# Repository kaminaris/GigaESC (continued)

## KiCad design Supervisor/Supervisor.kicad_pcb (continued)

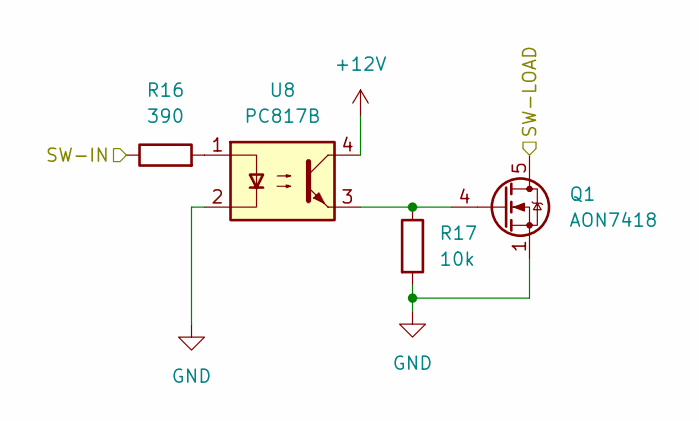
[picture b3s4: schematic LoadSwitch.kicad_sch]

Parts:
Q1: AON7418; VSON-8_3.3x3.3mm_P0.65mm_NexFET; MPN C74384
R16: 390; R_0603_1608Metric; MPN C23151
R17: 10k; R_0603_1608Metric; MPN C25804
U8: PC817B; SMDIP-4_W7.62mm; MPN C3025163

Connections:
+12V: U8.4; also elsewhere on the board
GND: Q1.1 (S), Q1.2 (S), Q1.3 (S), R17.2, U8.2; also elsewhere on the board
unnamed: Q1.4 (G), R17.1, U8.3
unnamed: R16.2, U8.1
SW1: R16.1; also elsewhere on the board
SW-LOAD-1: Q1.5 (D); also elsewhere on the board

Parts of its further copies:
Q2, Q3, Q4: AON7418; VSON-8_3.3x3.3mm_P0.65mm_NexFET; MPN C74384
R18, R20, R22: 390; R_0603_1608Metric; MPN C23151
R19, R21, R23: 10k; R_0603_1608Metric; MPN C25804
U9, U10, U11: PC817B; SMDIP-4_W7.62mm; MPN C3025163

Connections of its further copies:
+12V: U9.4, U10.4, U11.4; also elsewhere on the board
GND: Q2.1 (S), Q2.2 (S), Q2.3 (S), Q3.1 (S), Q3.2 (S), Q3.3 (S), Q4.1 (S), Q4.2 (S), Q4.3 (S), R19.2, R21.2, R23.2, U9.2, U10.2, U11.2; also elsewhere on the board
unnamed: Q2.4 (G), R19.1, U9.3
unnamed: Q3.4 (G), R21.1, U10.3
unnamed: Q4.4 (G), R23.1, U11.3
unnamed: R18.2, U9.1
unnamed: R20.2, U10.1
unnamed: R22.2, U11.1
SW2: R18.1; also elsewhere on the board
SW3: R20.1; also elsewhere on the board
SW4: R22.1; also elsewhere on the board
SW-LOAD-2: Q2.5 (D); also elsewhere on the board
SW-LOAD-3: Q3.5 (D); also elsewhere on the board
SW-LOAD-4: Q4.5 (D); also elsewhere on the board

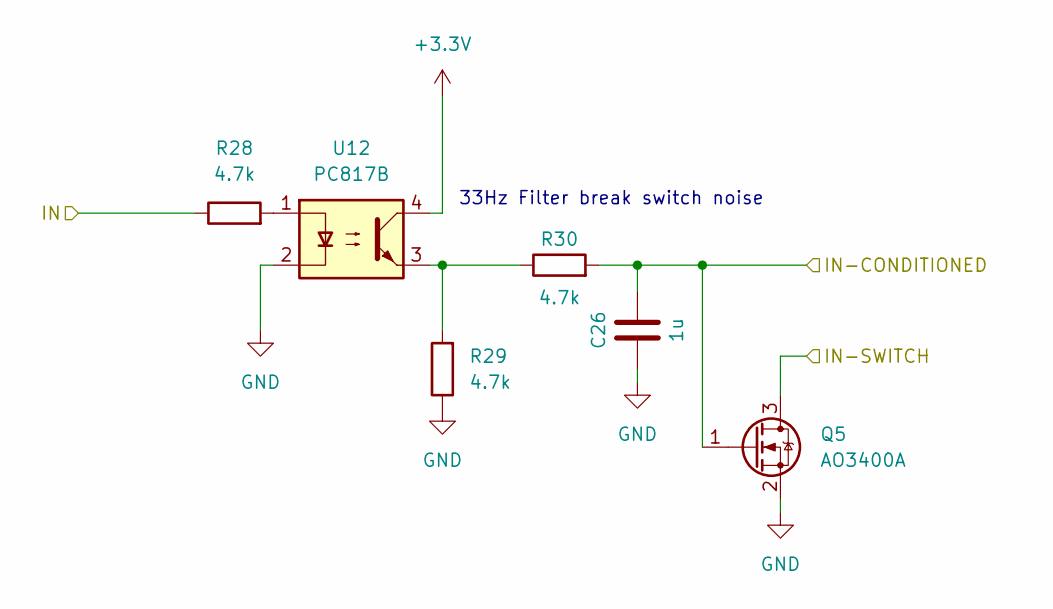
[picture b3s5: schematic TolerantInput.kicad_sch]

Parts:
C26: 1u; C_0603_1608Metric; MPN C15849
Q5: AO3400A; SOT-23; MPN C20917
R28, R29, R30: 4.7k; R_0603_1608Metric; MPN C23162
U12: PC817B; SMDIP-4_W7.62mm; MPN C3025163

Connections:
+3.3V: U12.4; also elsewhere on the board
D-IN-3: R28.1; also elsewhere on the board
DIGITAL-4-CLAMP: Q5.3 (D); also elsewhere on the board
GND: C26.2, Q5.2 (S), R29.1, U12.2; also elsewhere on the board
unnamed: R28.2, U12.1
unnamed: R29.2, R30.1, U12.3

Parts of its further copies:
C24: 1u; C_0603_1608Metric; MPN C15849
Q6: AO3400A; SOT-23; MPN C20917
R26, R27, R31: 4.7k; R_0603_1608Metric; MPN C23162
U13: PC817B; SMDIP-4_W7.62mm; MPN C3025163

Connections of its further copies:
+3.3V: U13.4; also elsewhere on the board
D-IN-4: R26.1; also elsewhere on the board
DIGITAL-3-CLAMP: Q6.3 (D); also elsewhere on the board
GND: C24.2, Q6.2 (S), R27.1, U13.2; also elsewhere on the board
unnamed: R26.2, U13.1
unnamed: R27.2, R31.1, U13.3

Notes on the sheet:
33Hz Filter break switch noise

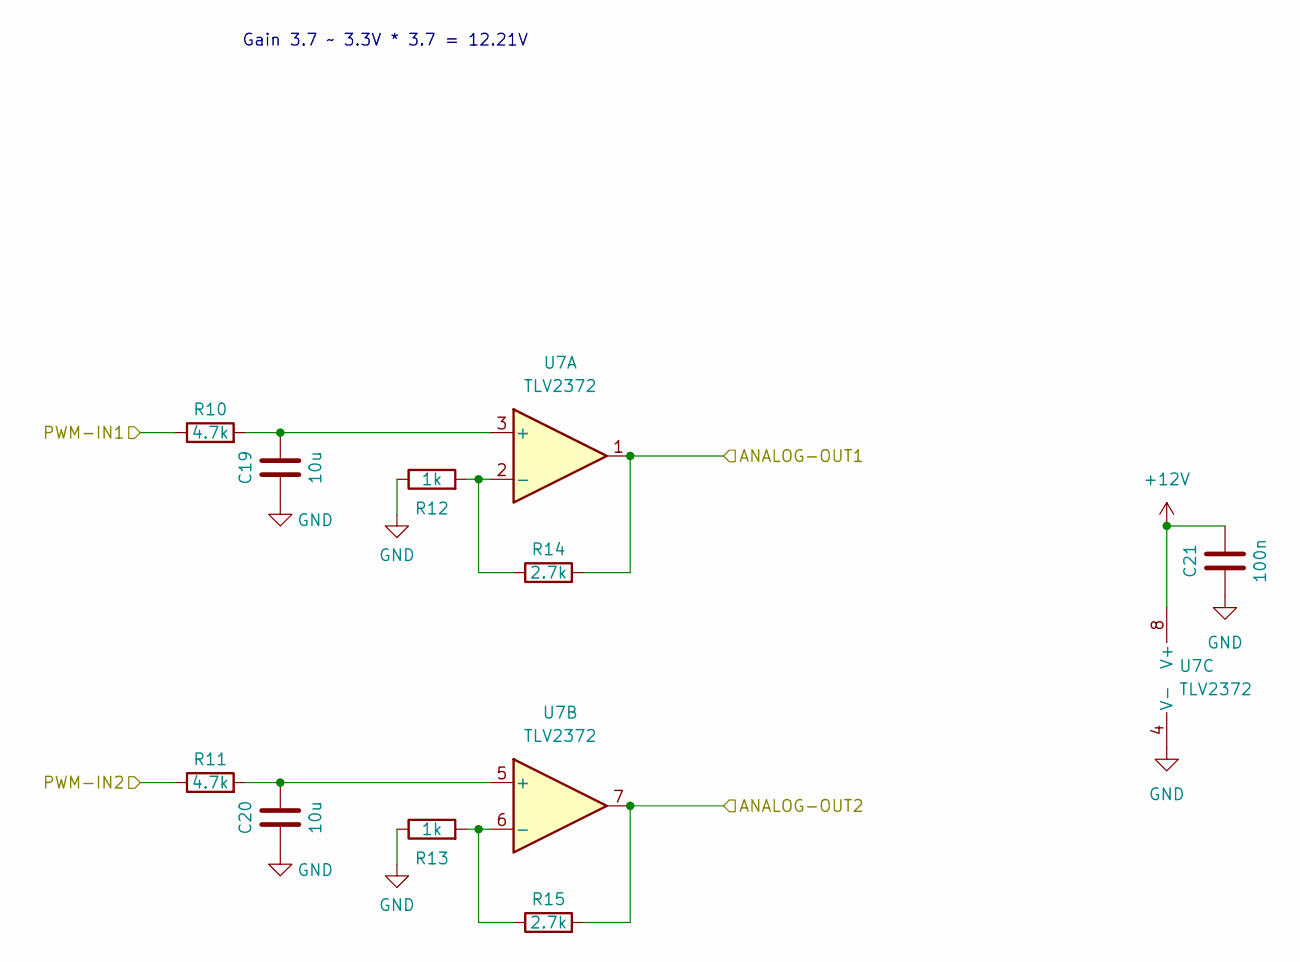
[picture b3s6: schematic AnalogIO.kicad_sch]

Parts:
C19, C20: 10u; C_0603_1608Metric; MPN C19702
C21: 100n; C_0603_1608Metric; MPN C14663
R10, R11: 4.7k; R_0603_1608Metric; MPN C23162
R12, R13: 1k; R_0603_1608Metric; MPN C21190
R14, R15: 2.7k; R_0603_1608Metric; MPN C13167
U7: TLV2372; SOIC-8_3.9x4.9mm_P1.27mm; MPN C27204

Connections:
+12V: C21.1, U7.8 (V+); also elsewhere on the board
AO1: R14.2, U7.1; also elsewhere on the board
AO2: R15.2, U7.7; also elsewhere on the board
GND: C19.2, C20.2, C21.2, R12.1, R13.1, U7.4 (V-); also elsewhere on the board
unnamed: C19.1, R10.2, U7.3 (+)
unnamed: R12.2, R14.1, U7.2 (-)
unnamed: C20.1, R11.2, U7.5 (+)
unnamed: R13.2, R15.1, U7.6 (-)
PWM1: R10.1; also elsewhere on the board
PWM2: R11.1; also elsewhere on the board

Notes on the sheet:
Gain 3.7 ~ 3.3V * 3.7 = 12.21V

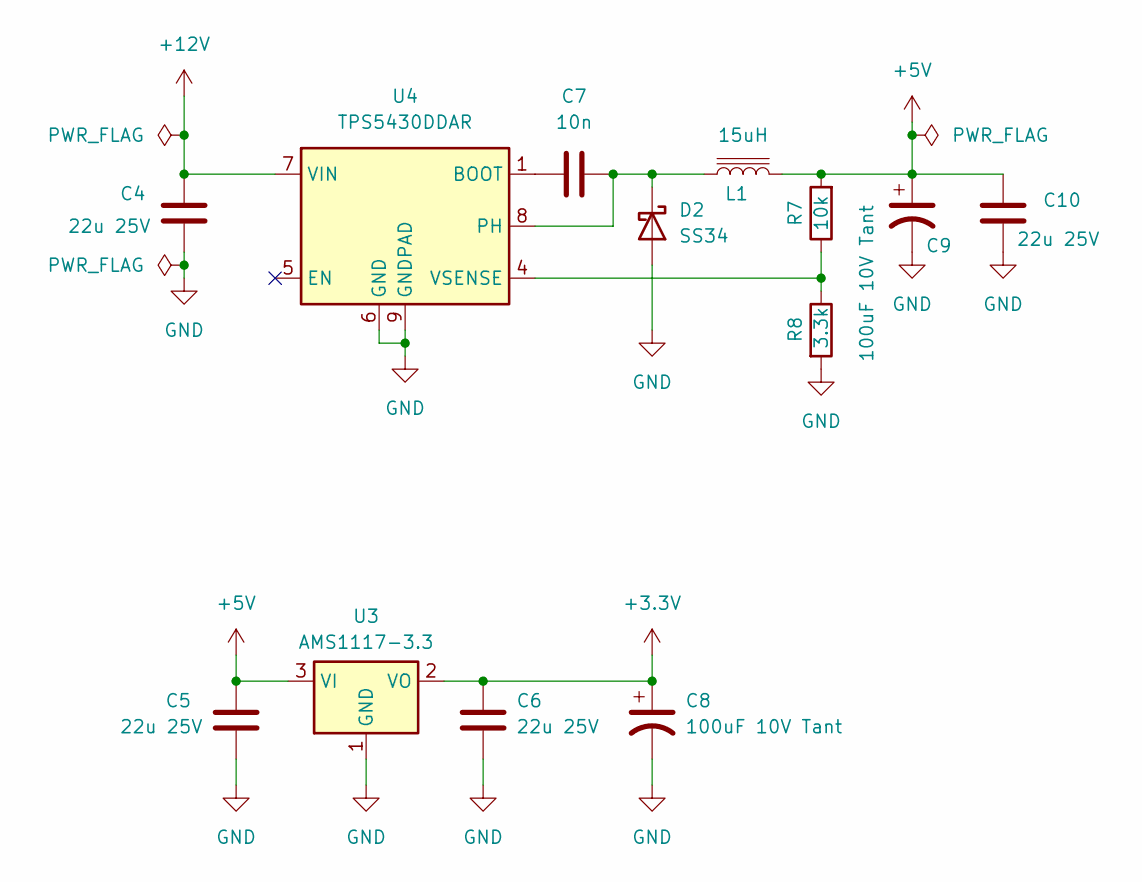
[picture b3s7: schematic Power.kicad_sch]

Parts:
C4, C5, C6, C10: 22u 25V; C_1206_3216Metric; MPN C12891
C7: 10n; C_0603_1608Metric; MPN C57112
C8, C9: 100uF 10V Tant; CP_EIA-6032-28_Kemet-C; MPN C171664; JLCRotOffset -180
D2: SS34; D_SMA; MPN C8678
L1: 15uH; L_Bourns_SRP7028A_7.3x6.6mm; MPN C177243
R7: 10k; R_0603_1608Metric; MPN C25804
R8: 3.3k; R_0603_1608Metric; MPN C22978
U3: AMS1117-3.3; SOT-223-3_TabPin2; MPN C6186; JLCRotOffset -180
U4: TPS5430DDAR; TI_SO-PowerPAD-8_ThermalVias; MPN C9864

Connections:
+3.3V: C6.1, C8.1, U3.2 (VO); also elsewhere on the board
+5V: C5.1, C9.1, C10.1, L1.2, R7.2, U3.3 (VI); also elsewhere on the board
+12V: C4.1, U4.7 (VIN); also elsewhere on the board
GND: C4.2, C5.2, C6.2, C8.2, C9.2, C10.2, D2.2 (A), R8.2, U3.1 (GND), U4.6 (GND), U4.9 (GNDPAD); also elsewhere on the board
unnamed: C7.1, D2.1 (K), L1.1, U4.8 (PH)
unnamed: C7.2, U4.1 (BOOT)
unnamed: R7.1, R8.1, U4.4 (VSENSE)

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
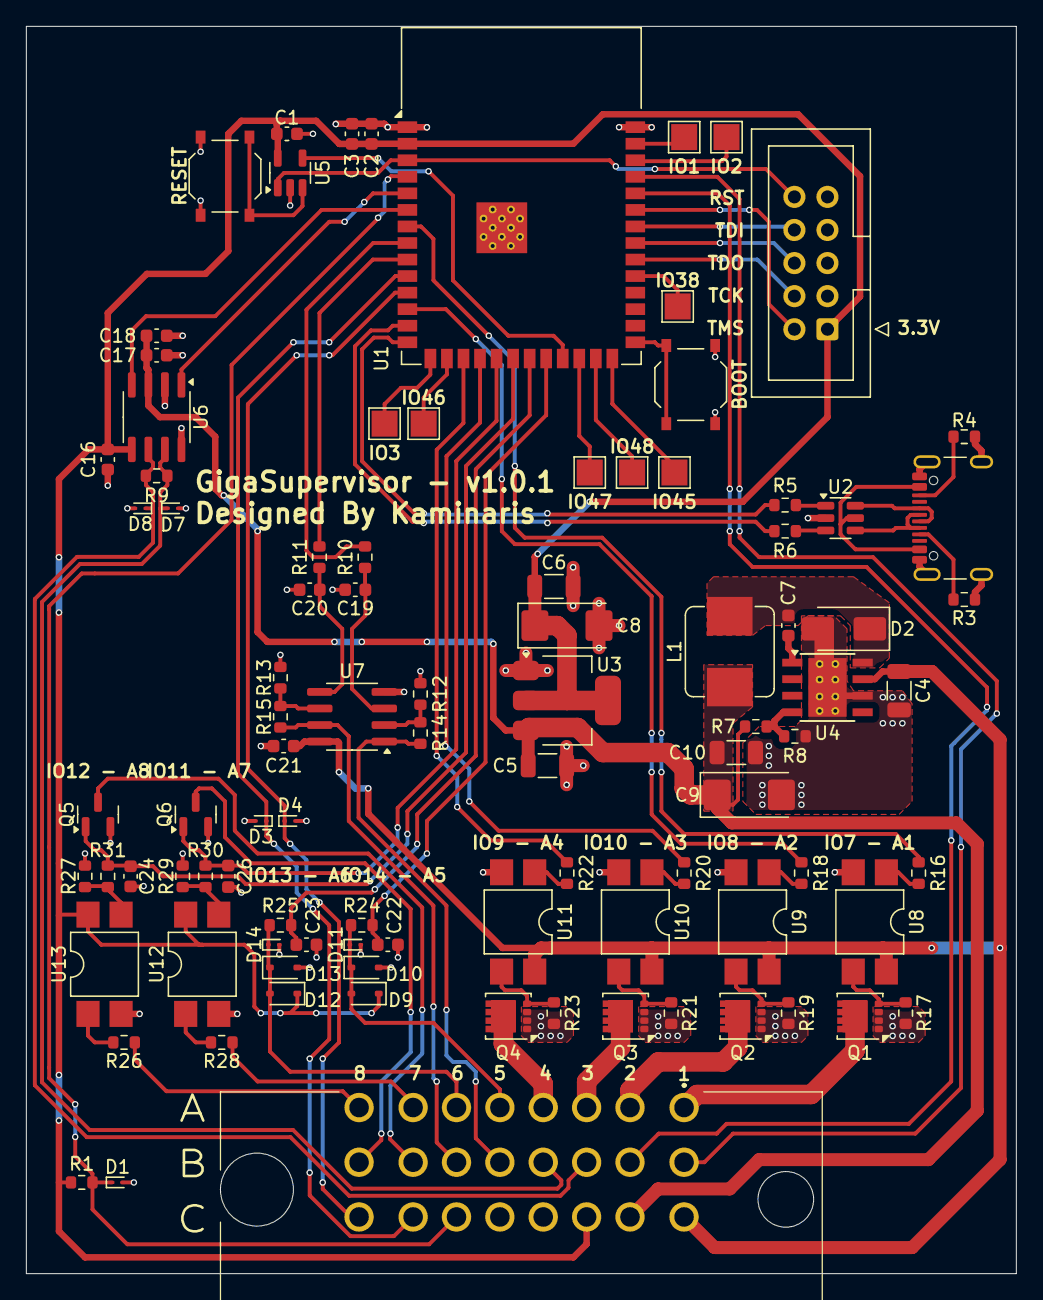
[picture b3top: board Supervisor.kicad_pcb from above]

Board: 2 copper layers, 76.0 x 95.8 mm, 97 parts (0 on the bottom side), 79 nets.

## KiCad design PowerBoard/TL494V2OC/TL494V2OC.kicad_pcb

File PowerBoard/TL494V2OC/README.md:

# Power Supply TL494 V2

Version without power switch

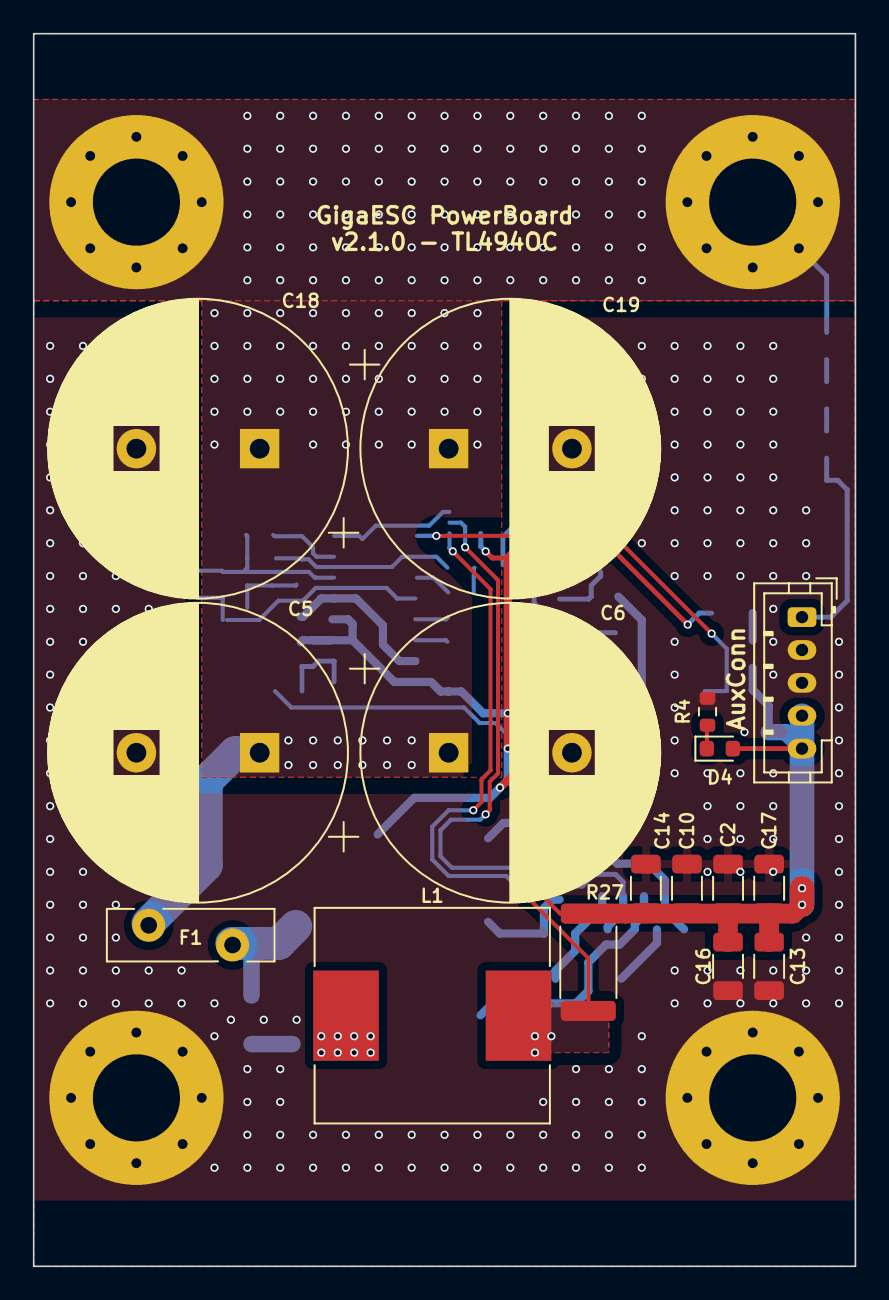
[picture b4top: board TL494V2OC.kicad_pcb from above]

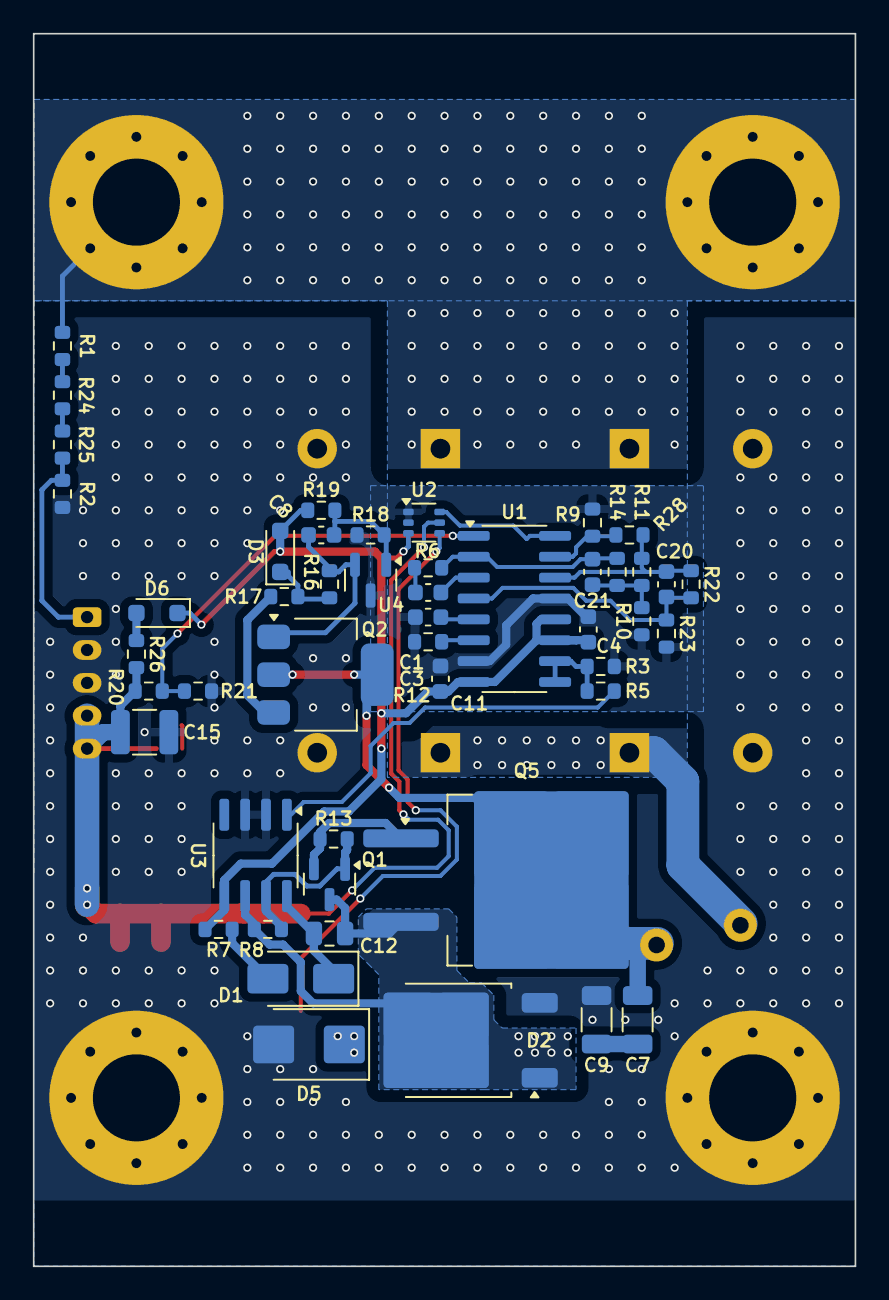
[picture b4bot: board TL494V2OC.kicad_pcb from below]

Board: 2 copper layers, 50.0 x 75.0 mm, 68 parts (48 on the bottom side), 34 nets.

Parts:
C1, C4, C21: 100n; C_0603_1608Metric
C2, C10, C13, C14, C16, C17: 22u; C_1206_3216Metric
C3, C8: 1n; C_0603_1608Metric
C5, C6, C18, C19: 330u 200V; CP_Radial_D18.0mm_P7.50mm
C7, C9: 2.2u 100V; C_1206_3216Metric
C11: 1u; C_0603_1608Metric
C12: 100n 200V; C_0805_2012Metric
C15: 47u 16V; C_1210_3225Metric
C20: 10u; C_0603_1608Metric
D1: SS520F; D_SMA
D2: CI04S65E3; TO-252-2
D3: BZT52C5V1S; D_SOD-323_HandSoldering
D4: RUN; D_0603_1608Metric
D5: BZG03C16-M3-08; D_SMB
D6: 1N5819WS; D_SOD-323_HandSoldering
F1: RLVR240-100; Fuse_Bourns_MF-RHT400
H1, H2, H3, H4: MountingHole_Pad; MountingHole_5.3mm_M5_Pad_Via
J1: AuxConn; JST_PH_B5B-PH-K_1x05_P2.00mm_Vertical
L1: 100uH; L_Chilisin_BMRG00131360
Q1: MMBTA92; SOT-23
Q2: CPC3980; SOT-223-3_TabPin2
Q5: IRFS4227TRLPBF; TO-263-2
R1, R24, R25: 348k; R_0603_1608Metric
R2: 18.7k; R_0603_1608Metric
R3, R16, R22: 10k; R_0603_1608Metric
R4: 82k; R_0603_1608Metric
R5: 100; R_0603_1608Metric
R6: 2k; R_0603_1608Metric
R7, R13, R26: 22; R_0603_1608Metric
R8: 1k; R_0603_1608Metric
R9, R10, R11, R12: 5.1k; R_0603_1608Metric
R14: 200k; R_0603_1608Metric
R17: 47; R_0603_1608Metric
R18: 9.1k; R_0603_1608Metric
R19: 30k; R_0603_1608Metric
R20: 100k; R_0603_1608Metric
R21: 27k; R_0603_1608Metric
R23: 4.7k; R_0603_1608Metric
R27: 10m; R_2512_6332Metric
R28: 20k; R_0603_1608Metric
U1: TL494; SOIC-16_3.9x9.9mm_P1.27mm
U2: INA213; SOT-363_SC-70-6
U3: IR2181; SOIC-8_3.9x4.9mm_P1.27mm
U4: TL431; SOT-23

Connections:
+12V: C2.1, C10.1, C13.1, C14.1, C15.1, C16.1, C17.1, D4.2 (A), J1.4, J1.5, R20.1, R26.1, R27.2, U2.5 (-)
+BATT: C5.1, C6.1, C18.1, C19.1, F1.1, H2.1, H4.1, R1.1
+VSW: C7.1, F1.2, Q2.2 (D), Q5.2 (D)
-BATT: C2.2, C3.2, C4.2, C5.2, C6.2, C9.2, C10.2, C11.2, C13.2, C14.2, C15.2, C16.2, C17.2, C18.2, C19.2, D2.3 (A), D5.2 (A), H1.1, H3.1, J1.2, J1.3, R2.2, R3.2, R4.1, R9.2, R10.2, R12.2, R18.2, R21.2, R23.2, U1.7 (GND), U1.13 (OUTCTRL), U2.1 (REF), U2.2 (GND), U3.2 (LIN), U3.3 (COM), U4.3 (A)
/SW-NODE: C12.2, D2.1 (K), D2.2 (K), L1.1, Q1.3 (C), Q5.3 (S), R8.1, U3.6 (VS)
CFB: U1.16 (2IN+), U2.6
CFB-: R9.1, R28.2, U1.15 (2IN-)
DRV-OUT: Q1.1 (B), R8.2, R13.1, U3.7 (HO)
IN_V: J1.1, R2.1, R25.2
unnamed: C1.1, R6.2
unnamed: C7.2, C9.1
unnamed: C21.2, R10.1, R11.2, R14.2
unnamed: D1.2 (A), R7.2
unnamed: C12.1, D1.1 (K), U3.8 (VB)
unnamed: D3.1 (K), R16.1, R17.2
unnamed: D4.1 (K), R4.2
unnamed: D5.1 (K), L1.2, R27.1, U2.4 (+)
unnamed: D6.2 (A), R26.2
unnamed: Q1.2 (E), Q5.1 (G), R13.2
unnamed: C8.1, Q2.1 (G), R16.2, U4.2 (K)
unnamed: Q2.3 (S), R17.1
unnamed: R1.2, R24.1
unnamed: R24.2, R25.1
unnamed: C21.1, R6.1, R14.1, U1.2 (1IN-)
unnamed: C3.1, U1.5 (CT)
unnamed: C20.2, R22.2, R23.1, U1.4 (DTC)
unnamed: R3.1, R5.2, U1.9 (E1), U1.10 (E2)
unnamed: C1.2, U1.3 (FB)
unnamed: C20.1, R11.1, R22.1, R28.1, U1.14 (REF)
unnamed: R12.1, U1.6 (RT)
unnamed: R5.1, U3.1 (HIN)
unnamed: C8.2, R18.1, R19.1, U4.1 (R)
STARTUP: C4.1, C11.1, D3.2 (A), D6.1 (K), R7.1, R19.2, U1.8 (C1), U1.11 (C2), U1.12 (VCC), U2.3 (V+), U3.5 (VCC)
VFB: R20.2, R21.1, U1.1 (1IN+)

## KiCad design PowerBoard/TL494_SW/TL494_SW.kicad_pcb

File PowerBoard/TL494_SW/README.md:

# Power Supply TL494

Version with power switch

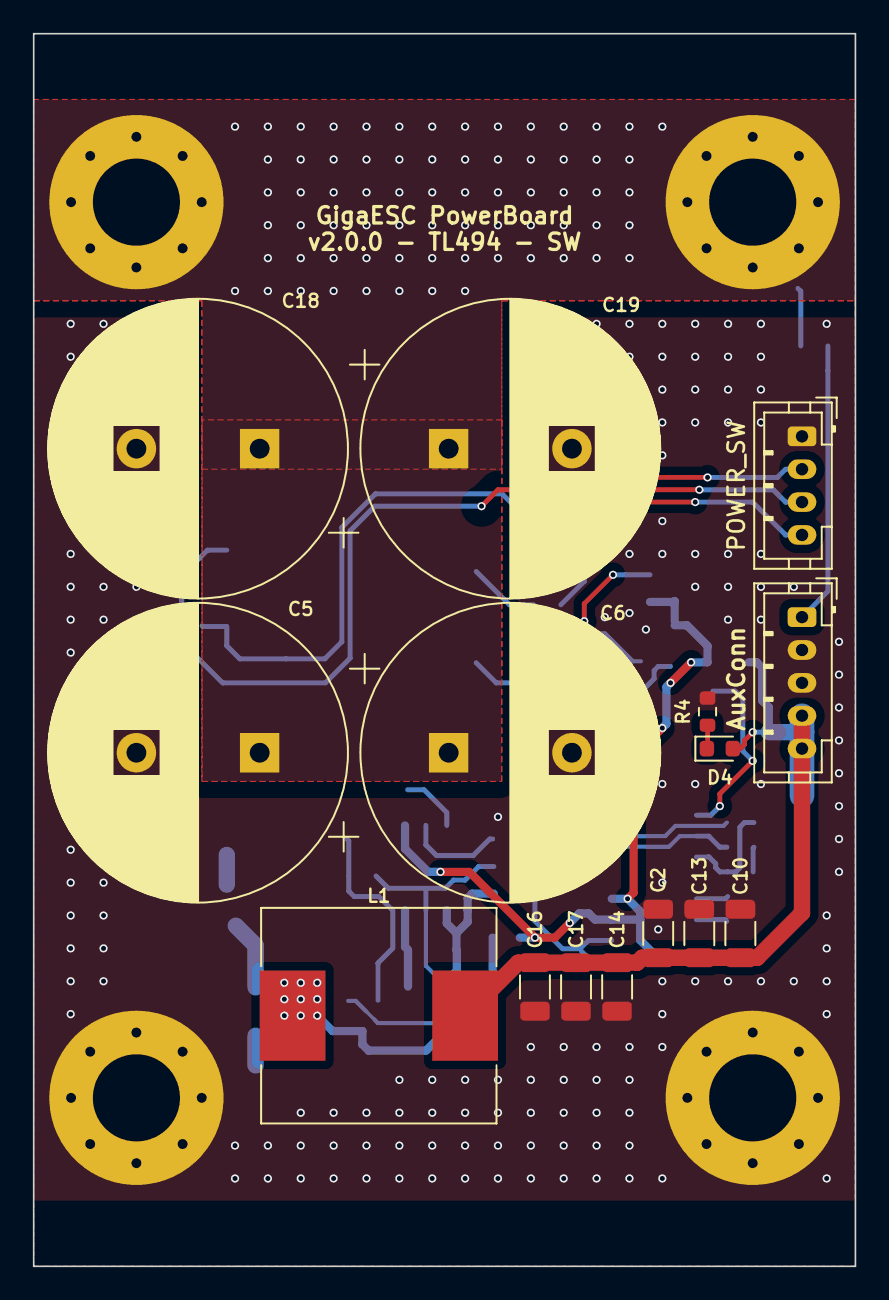
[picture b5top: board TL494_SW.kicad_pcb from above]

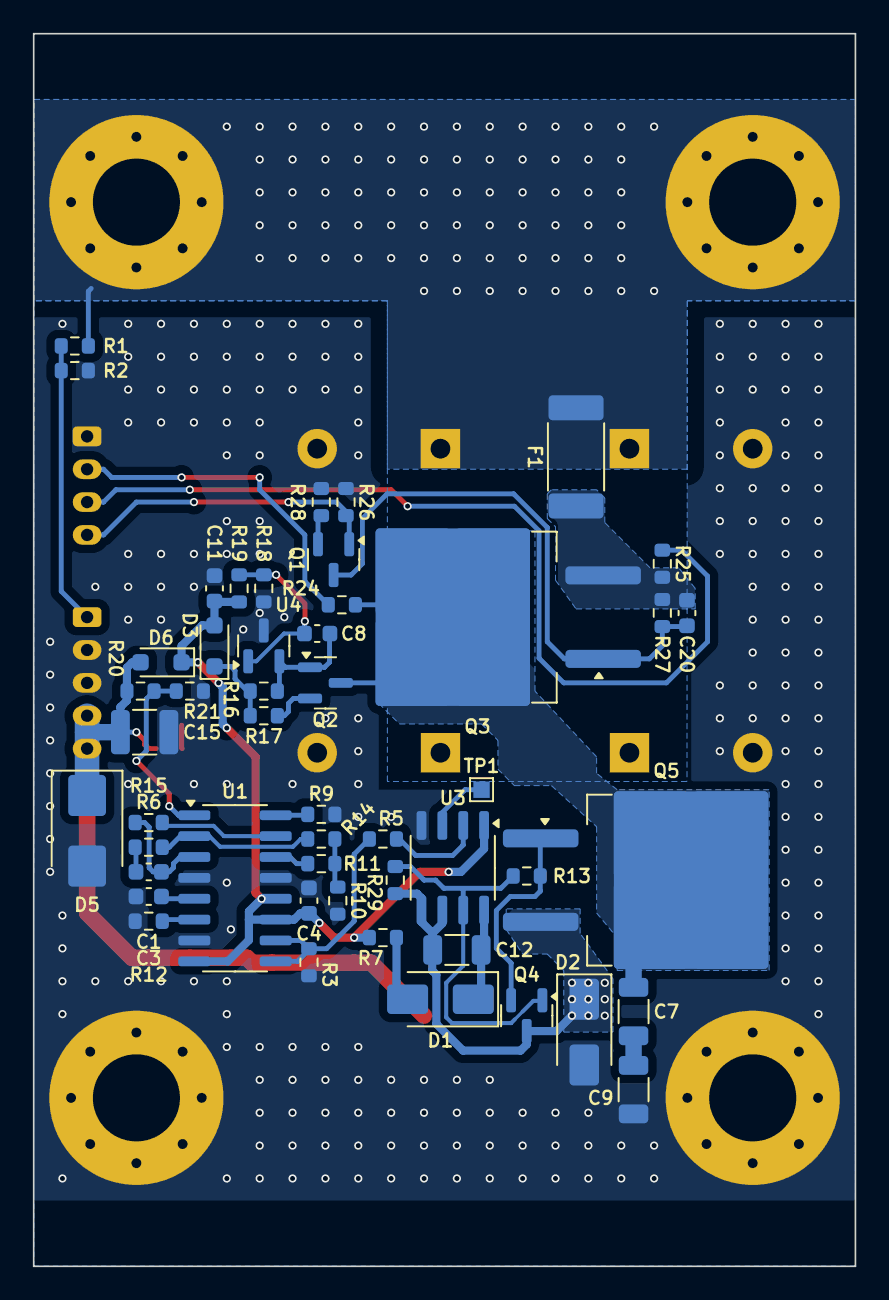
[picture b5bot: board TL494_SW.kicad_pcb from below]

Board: 2 copper layers, 50.0 x 75.0 mm, 69 parts (50 on the bottom side), 36 nets.

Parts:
C1, C4, C20: 100n; C_0603_1608Metric
C2, C10, C13, C14, C16, C17: 22u; C_1206_3216Metric
C3, C8: 1n; C_0603_1608Metric
C5, C6, C18, C19: 330u 200V; CP_Radial_D18.0mm_P7.50mm
C7, C9: 2.2u 100V; C_1206_3216Metric
C11: 1u; C_0603_1608Metric
C12: 220n; C_1206_3216Metric
C15: 47u 16V; C_1210_3225Metric
D1, D2: SS520F; D_SMA
D3: BZT52C5V1S; D_SOD-323_HandSoldering
D4: RUN; D_0603_1608Metric
D5: 3SMB5928B; D_SMB
D6: 1N5819WS; D_SOD-323_HandSoldering
F1: Fuse; Fuse_2512_6332Metric_Pad1.52x3.35mm_HandSolder
H1, H2, H3, H4: MountingHole_Pad; MountingHole_5.3mm_M5_Pad_Via
J1: AuxConn; JST_PH_B5B-PH-K_1x05_P2.00mm_Vertical
J2: POWER_SW; JST_PH_B4B-PH-K_1x04_P2.00mm_Vertical
L1: 100uH; L_Chilisin_BMRG00131360
Q1: MMBTA42; SOT-23
Q2: BSS126; SOT-23
Q3: IRF9640SPBF; TO-263-2
Q4: S9012 2T1; SOT-23
Q5: IRFS4227TRLPBF; TO-263-2
R1: 150k; R_0603_1608Metric
R2, R21: 2.7k; R_0603_1608Metric
R3, R15, R16, R18, R20: 10k; R_0603_1608Metric
R4: 82k; R_0603_1608Metric
R5, R9, R17: 100; R_0603_1608Metric
R6: 2k; R_0603_1608Metric
R7, R13: 22; R_0603_1608Metric
R10, R11, R12: 5.1k; R_0603_1608Metric
R14, R25: 200k; R_0603_1608Metric
R19: 30k; R_0603_1608Metric
R24, R27: 100k; R_0603_1608Metric
R26: 20k; R_0603_1608Metric
R28: 27k; R_0603_1608Metric
R29: 1k; R_0603_1608Metric
TP1: TestPoint; TestPoint_Pad_1.0x1.0mm
U1: TL494; SOIC-16_3.9x9.9mm_P1.27mm
U3: IRS21271; SO-8_3.9x4.9mm_P1.27mm
U4: TL431; SOT-23

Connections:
+12V: C2.1, C10.1, C13.1, C14.1, C15.1, C16.1, C17.1, D4.2 (A), D5.1 (K), D6.2 (A), J1.4, J1.5, L1.2, R20.2
+BATT: C5.1, C6.1, C18.1, C19.1, F1.1, H2.1, H4.1, R1.1
+VSW: C7.1, Q2.3 (D), Q3.2 (D), Q5.2 (D), R24.2
-BATT: C2.2, C3.2, C4.2, C5.2, C6.2, C9.2, C10.2, C11.2, C13.2, C14.2, C15.2, C16.2, C17.2, C18.2, C19.2, D2.2 (A), D5.2 (A), H1.1, H3.1, J1.2, J1.3, J2.1, R2.2, R3.2, R4.1, R9.1, R10.2, R12.2, R18.1, R21.1, R26.2, R28.2, U1.4 (DTC), U1.7 (GND), U1.13 (OUTCTRL), U3.4 (COM), U4.3 (A)
BOOTSTRAP: C4.1, C11.1, D3.2 (A), D6.1 (K), R7.1, R19.2, U1.8 (C1), U1.11 (C2), U1.12 (VCC), U3.1 (VCC)
IN_V: J1.1, R1.2, R2.1
unnamed: C1.1, R6.2
unnamed: C7.2, C9.1
unnamed: D1.2 (A), R7.2
unnamed: C12.1, D1.1 (K), U3.8 (VB)
unnamed: C12.2, D2.1 (K), L1.1, Q4.3 (C), Q5.3 (S), R29.1, U3.5 (VS), U3.6 (CS)
unnamed: D3.1 (K), R16.1, R17.1
unnamed: D4.1 (K), R4.2
unnamed: J2.2, R24.1
unnamed: J2.3, R25.2
unnamed: J2.4, Q1.1 (B), R26.1
unnamed: C20.2, Q1.3 (C), Q3.1 (G), R27.2
unnamed: Q1.2 (E), R28.1
unnamed: C8.1, Q2.1 (G), R16.2, U4.2 (K)
unnamed: Q2.2 (S), R17.2
unnamed: C20.1, F1.2, Q3.3 (S), R25.1, R27.1
unnamed: Q4.1 (B), R13.1, R29.2, U3.7 (HO)
unnamed: Q4.2 (E), Q5.1 (G), R13.2
unnamed: R10.1, R11.2, R14.2
unnamed: R6.1, R14.1, U1.2 (1IN-)
unnamed: R9.2, U1.16 (2IN+)
unnamed: R15.2, U1.15 (2IN-)
unnamed: C3.1, U1.5 (CT)
unnamed: R3.1, R5.2, U1.9 (E1), U1.10 (E2)
unnamed: C1.2, R15.1, U1.3 (FB)
unnamed: R11.1, U1.14 (REF)
unnamed: R12.1, U1.6 (RT)
unnamed: TP1.1, U3.3 (FAULT)
unnamed: R5.1, U3.2 (IN)
unnamed: C8.2, R18.2, R19.1, U4.1 (R)
VFB: R20.1, R21.2, U1.1 (1IN+)

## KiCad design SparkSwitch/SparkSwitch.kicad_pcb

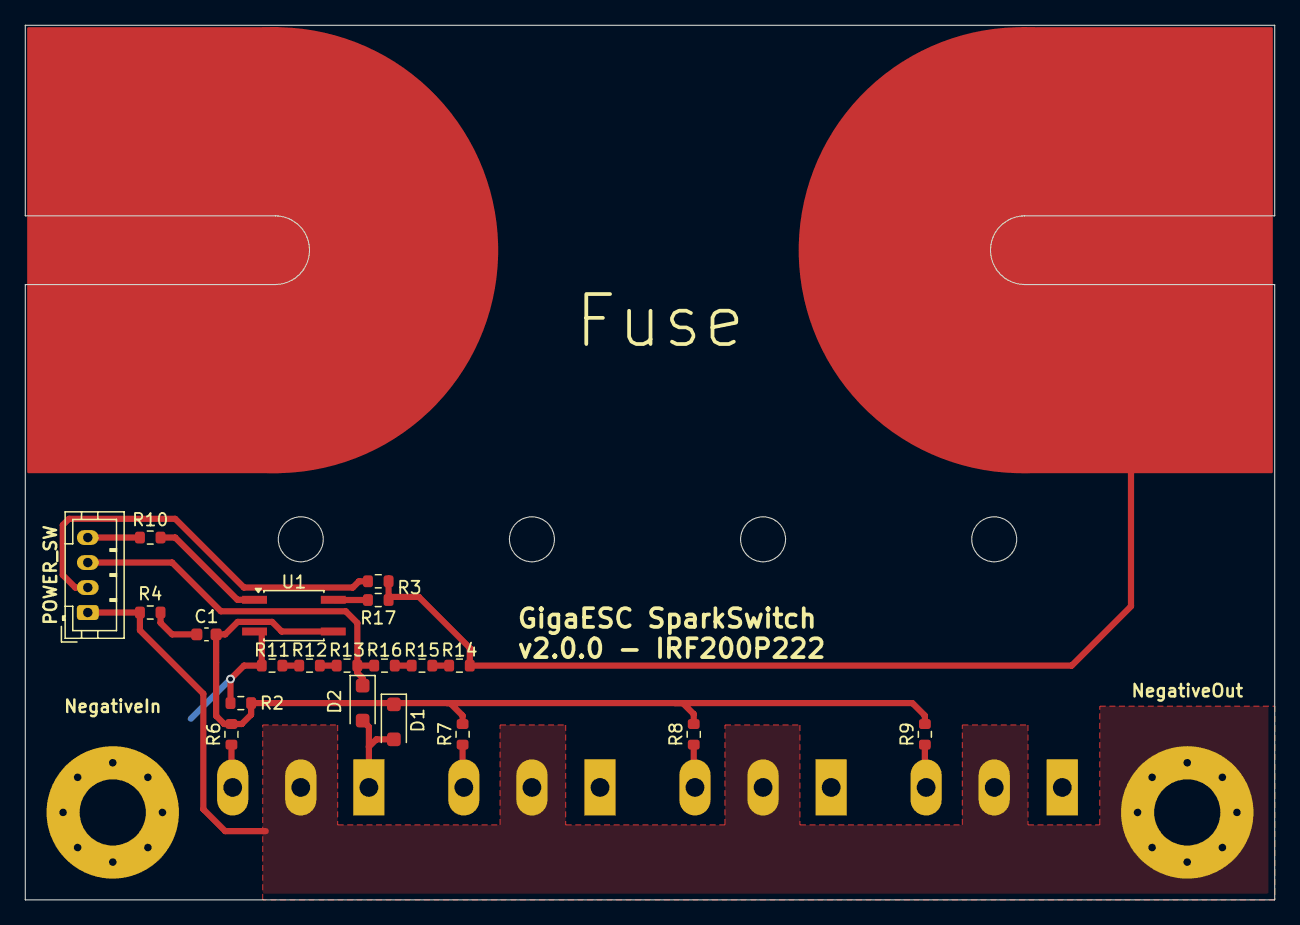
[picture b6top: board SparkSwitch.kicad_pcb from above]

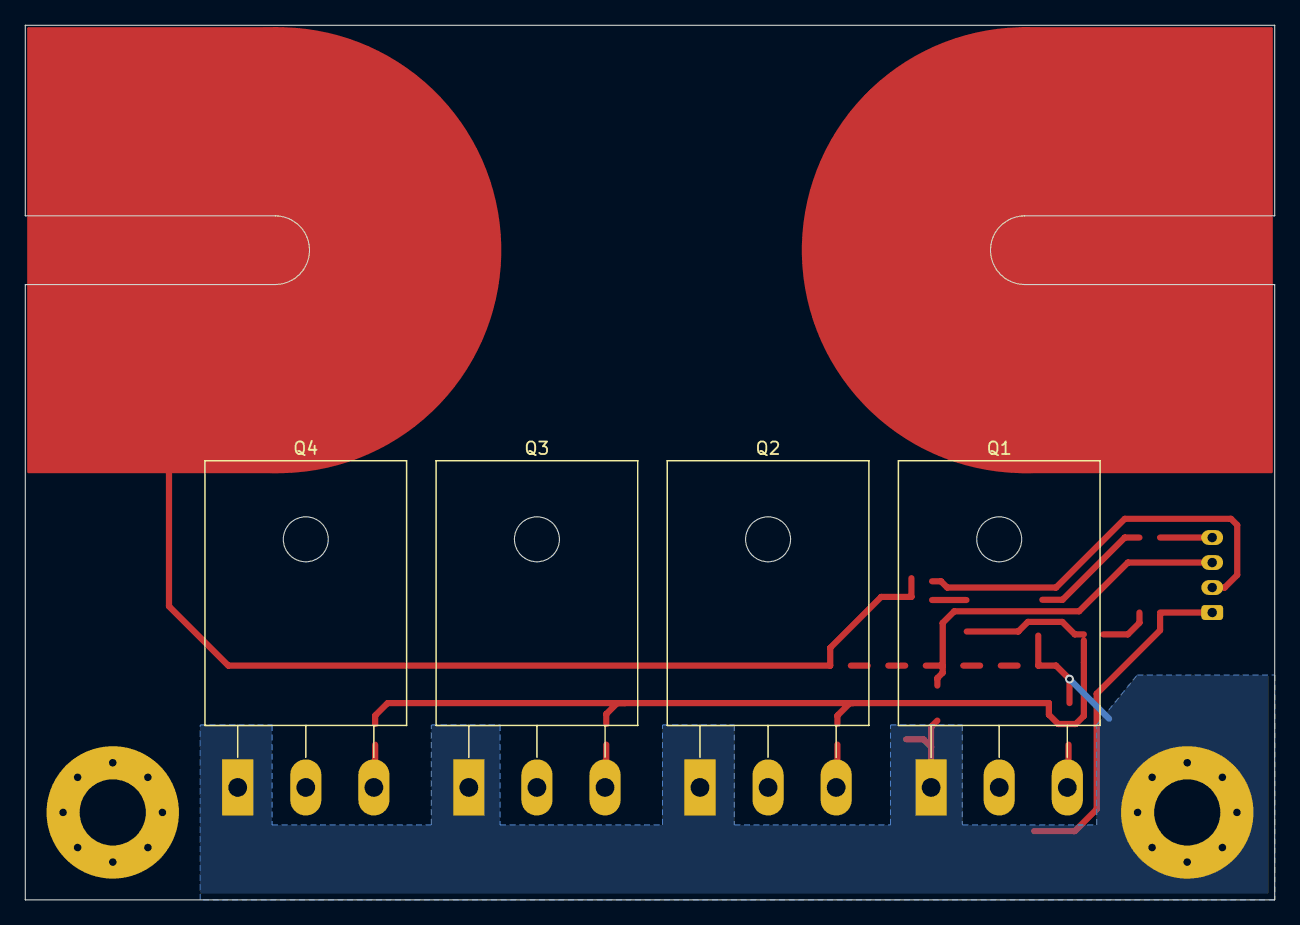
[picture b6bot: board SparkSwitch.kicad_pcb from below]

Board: 2 copper layers, 100.0 x 70.0 mm, 27 parts (4 on the bottom side), 18 nets.

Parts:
C1: 1u; C_0603_1608Metric
D1, D2: BZT52B12; D_SOD-123F
J3: POWER_SW; JST_PH_B4B-PH-K_1x04_P2.00mm_Vertical
J5: NegativeIn; MountingHole_5.3mm_M5_Pad_Via
J7: NegativeOut; MountingHole_5.3mm_M5_Pad_Via
Q1, Q2, Q3, Q4: IRF200P222; TO-247-3_Horizontal_TabDown
R2: 10k; R_0603_1608Metric
R3, R11, R12, R13, R14, R15, R16: 100k; R_0603_1608Metric
R4, R17: 1k; R_0603_1608Metric
R6, R7, R8, R9, R10: 22; R_0603_1608Metric
TP1: TestPoint; TestPoint_Pad_1.0x1.0mm
U1: LTV-352T; SO-4_4.4x3.6mm_P2.54mm

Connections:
+VSW: R3.2, R14.1, R17.1
-BATT: J3.1, J7.1, Q1.2 (D), Q2.2 (D), Q3.2 (D), Q4.2 (D), R4.2
GND: D1.2 (A), D2.2 (A), J5.1, Q1.1 (S), Q2.1 (S), Q3.1 (S), Q4.1 (S), R2.2, R11.2, U1.2
unnamed: C1.1, R4.1
unnamed: C1.2, D1.1 (K), R2.1, R6.2, R7.2, R8.2, R9.2, U1.3
unnamed: J3.2, R3.1
unnamed: Q1.3 (G), R6.1
unnamed: Q2.3 (G), R7.1
unnamed: Q3.3 (G), R8.1
unnamed: Q4.3 (G), R9.1
unnamed: R10.2, U1.1
unnamed: R11.1, R12.2
unnamed: R12.1, R13.2
unnamed: R14.2, R15.1
unnamed: R15.2, R16.1
unnamed: R17.2, U1.4
SW_NC: J3.4, R10.1
SW_NX: D2.1 (K), J3.3, R13.1, R16.2

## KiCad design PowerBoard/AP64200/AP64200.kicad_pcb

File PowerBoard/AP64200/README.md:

# Power Supply AP64200

## ⚠ Not working - Do not use ⚠

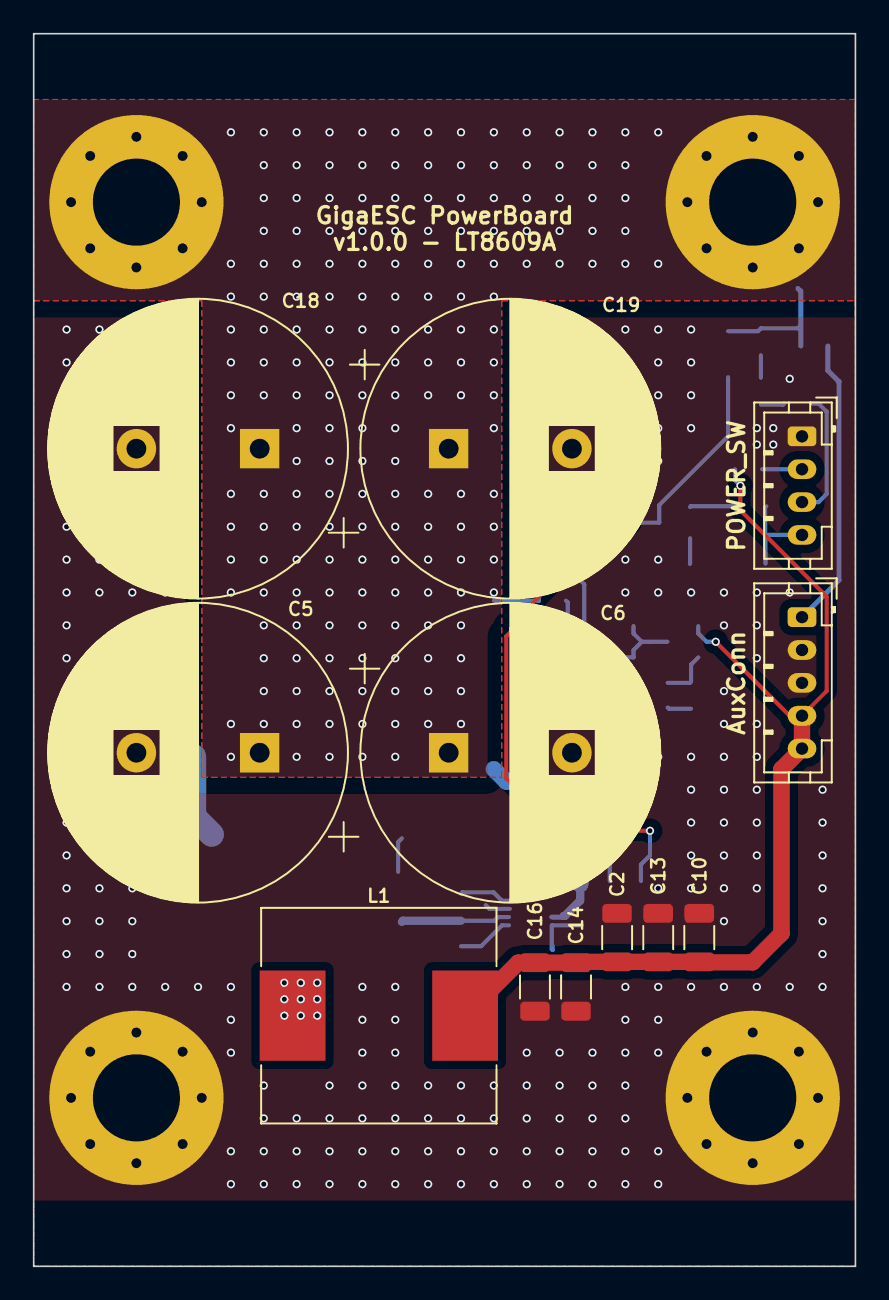
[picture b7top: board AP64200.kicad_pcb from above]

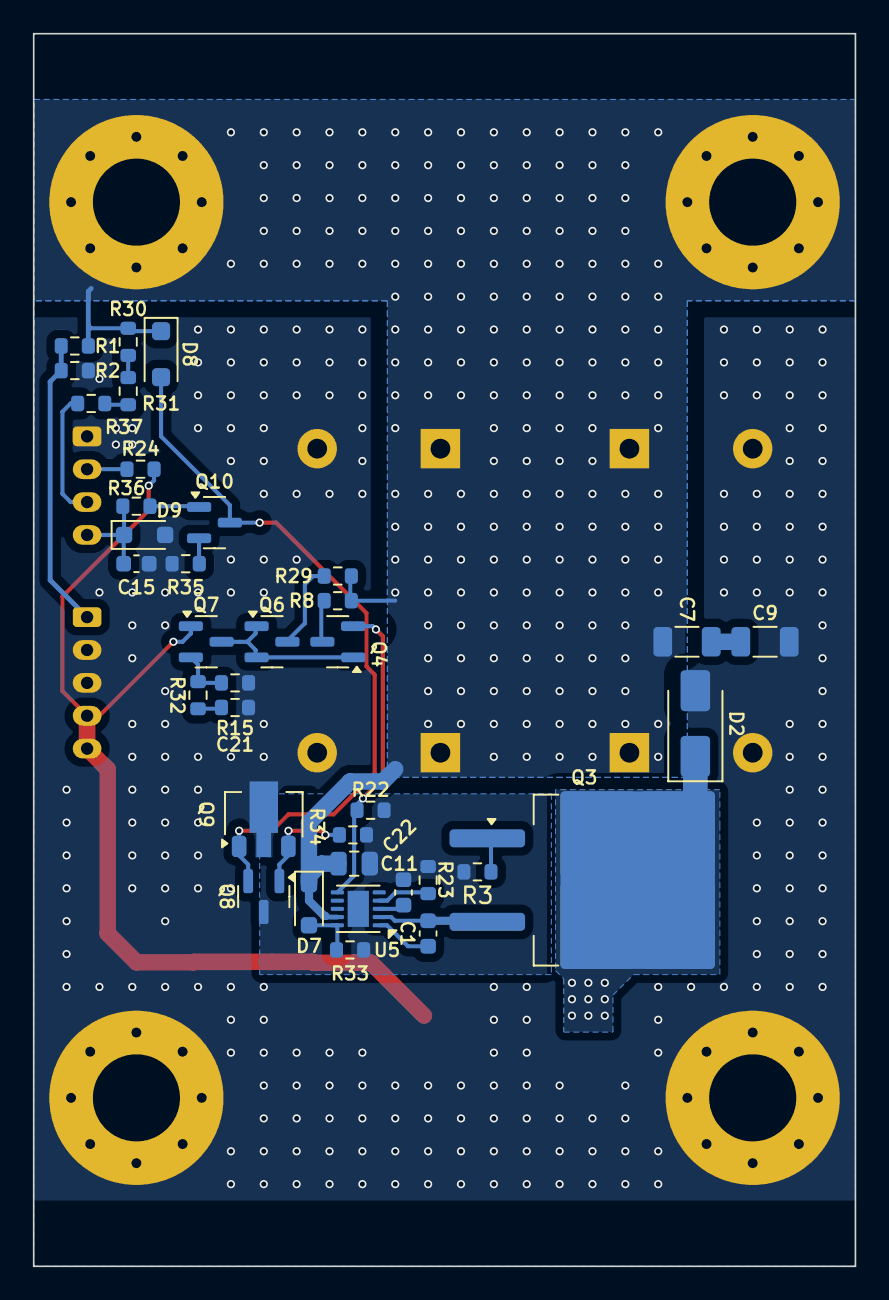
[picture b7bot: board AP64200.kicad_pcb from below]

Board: 2 copper layers, 50.0 x 75.0 mm, 52 parts (36 on the bottom side), 28 nets.

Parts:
C1, C15: 100n; C_0603_1608Metric
C2, C10, C13, C14, C16: 22u; C_1206_3216Metric
C5, C6, C18, C19: 330u 200V; CP_Radial_D18.0mm_P7.50mm
C7, C9: 2.2u 100V; C_1206_3216Metric
C11: 1u; C_0603_1608Metric
C21: 22n; C_0603_1608Metric_L
C22: 10u; C_0805_2012Metric
D2: SS520F; D_SMA
D7, D9: BZT52C8V2S; D_SOD-323_HandSoldering
D8: BZT52B12; D_SOD-123F
H1, H2, H3, H4: MountingHole_Pad; MountingHole_5.3mm_M5_Pad_Via
J1: AuxConn; JST_PH_B5B-PH-K_1x05_P2.00mm_Vertical
J2: POWER_SW; JST_PH_B4B-PH-K_1x04_P2.00mm_Vertical
L1: 100uH; L_Chilisin_BMRG00131360
Q3: IRF9640SPBF; TO-263-2
Q4, Q6, Q8: S9012 2T1; SOT-23
Q7, Q10: MMBTA42; SOT-23
Q9: MMBTA92T; SOT-89-3
R1: 150k; R_0603_1608Metric
R2: 2.7k; R_0603_1608Metric
R3: 22; R_0603_1608Metric
R8, R29: 1k; R_0603_1608Metric
R15, R33: 10k; R_0603_1608Metric
R22, R32: 820; R_0603_1608Metric
R23: 220k; R_0603_1608Metric
R24, R30, R31, R37: 100k; R_0603_1608Metric
R34: 150; R_0603_1608Metric
R35: 4.7k; R_0603_1608Metric
R36: 30k; R_0603_1608Metric
U5: LT8609AJDDM; DFN-10-1EP_2.6x2.6mm_P0.5mm_EP1.3x2.2mm

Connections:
+12V: C2.1, C10.1, C13.1, C14.1, C16.1, J1.4, J1.5, L1.2, Q7.1 (B), R24.2
+BATT: C5.1, C6.1, C7.1, C18.1, C19.1, C22.1, D7.1 (K), D8.1 (K), H2.1, H4.1, R1.1, R8.2, R29.2, R30.1, U5.9 (VIN)
-BATT: C2.2, C5.2, C6.2, C9.2, C10.2, C13.2, C14.2, C15.1, C16.2, C18.2, C19.2, C21.2, D2.2 (A), D9.2 (A), H1.1, H3.1, J1.2, J1.3, J2.1, Q9.2 (C), R2.2, R15.1, R35.2
GNDH: C11.2, C22.2, Q8.3 (E), R3.2, R22.1, R23.2, R33.1, R34.1, U5.11 (GND)
IN_V: J1.1, R1.2, R2.1
unnamed: C7.2, C9.1
unnamed: C21.1, R32.1
unnamed: D2.1 (K), L1.1, Q3.2 (D)
unnamed: D7.2 (A), R33.2, U5.10 (EN/UV)
unnamed: D8.2 (A), Q8.2 (C), Q9.1 (B), Q10.3 (C)
unnamed: C15.2, D9.1 (K), J2.4, R36.1
unnamed: J2.2, R24.1
unnamed: J2.3, R37.2
unnamed: Q3.1 (G), R3.1
unnamed: C1.1, Q3.3 (S), U5.2 (SW)
unnamed: Q4.1 (B), Q6.1 (B), Q6.2 (C), Q7.3 (C)
unnamed: Q4.2 (C), R22.2, U5.6 (FB)
unnamed: Q4.3 (E), R8.1
unnamed: Q6.3 (E), R29.1
unnamed: Q7.2 (E), R15.2, R32.2
unnamed: Q8.1 (B), Q9.3 (E), R34.2
unnamed: Q10.1 (B), R36.2
unnamed: Q10.2 (E), R35.1
unnamed: R30.2, R31.1
unnamed: R31.2, R37.1
unnamed: C1.2, U5.1 (BST)
unnamed: C11.1, U5.3 (INTVCC)
unnamed: R23.1, U5.4 (RT)
